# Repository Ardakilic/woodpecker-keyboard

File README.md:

# Woodpecker Keyboard
5 row ortholinear keyboard, based on [Lumberelite](https://github.com/tjeffree/lumberelite) and [Lumberjack](https://github.com/peej/lumberjack-keyboard).

The fork is done in a way that a wireless controller such as [nice!nano](https://nicekeyboards.com/nice-nano/) or [alternatives](https://github.com/joric/nrfmicro/wiki/Alternatives) could be utilized, and OLED module, Pimoroni Trackball or Cirque Trackpad could be applied over to the central area of the keyboard.

All work on the PCB is done by [Özkan Çelik](https://github.com/ozkan), he made this due to my request.

Shields are done by Kazim Kaba and [Ender Piyale](https://github.com/enderpiyale/).

[The plates of Lumberjack Keyboard](https://github.com/peej/lumberjack-keyboard/tree/master/plates) work nicely. I'm currently using the `lumberjack-split` flavour on my board, which you can also find [here](./plates-shields/plates/lumberjack-split.dxf).

Additionally, the board is compatible with 60% cases. My case is a wooden one from a Chinese e-commerce website. I raised the micro controller with sockets to not to drill a hole into my case.

## Firmware

* QMK: Keyboard definition and userspace
    * https://github.com/Ardakilic/qmk_firmware/tree/master/keyboards/woodpecker
    * https://github.com/Ardakilic/qmk_userspace/tree/main/keyboards/woodpecker
* ZMK: https://github.com/ardakilic/zmk-config-woodpecker

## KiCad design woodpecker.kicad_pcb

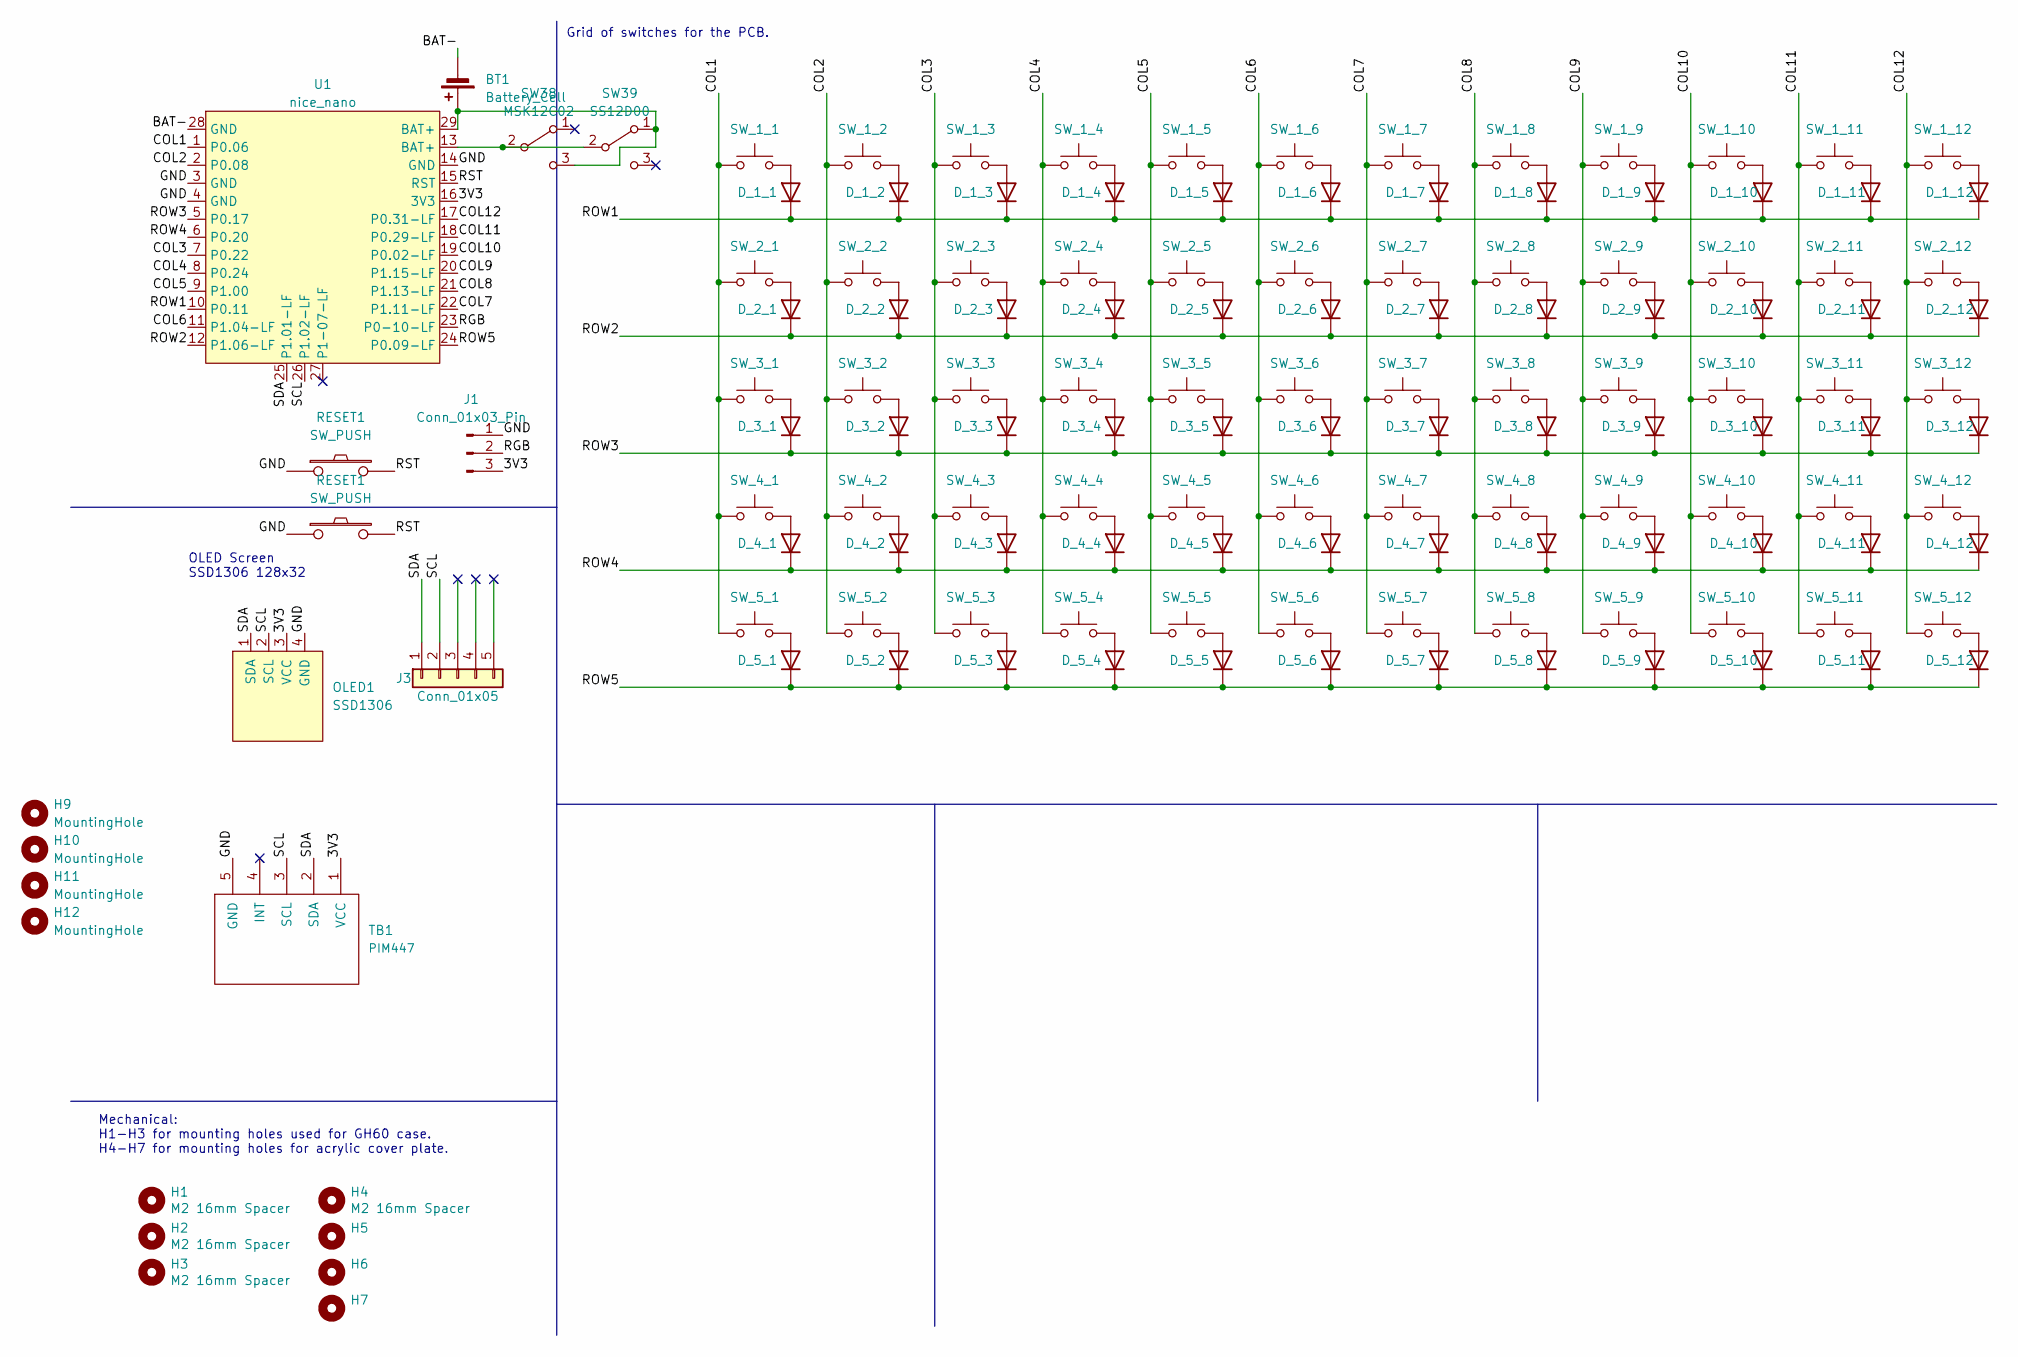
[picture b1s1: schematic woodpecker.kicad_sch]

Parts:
BT1: Battery_Cell; PinHeader_1x02_P2.54mm_Vertical
D_1_1, D_1_2, D_1_3, D_1_4, D_1_5, D_1_6, D_1_7, D_1_8, D_1_9, D_1_10, D_1_11, D_1_12, D_2_1, D_2_2, D_2_3, D_2_4, D_2_5, D_2_6, D_2_7, D_2_8, D_2_9, D_2_10, D_2_11, D_2_12, D_3_1, D_3_2, D_3_3, D_3_4, D_3_5, D_3_6, D_3_7, D_3_8, D_3_9, D_3_10, D_3_11, D_3_12, D_4_1, D_4_2, D_4_3, D_4_4, D_4_5, D_4_6, D_4_7, D_4_8, D_4_9, D_4_10, D_4_11, D_4_12, D_5_1, D_5_2, D_5_3, D_5_4, D_5_5, D_5_6, D_5_7, D_5_8, D_5_9, D_5_10, D_5_11, D_5_12: 1N4148; Diode-dual
H1, H2, H3, H4: M2 16mm Spacer; MountingHole_2.2mm_M2_DIN965_Pad
H5: Bumpon_3M_F0502
H6, H7: MountingHole_2.2mm_M2_elongated
H9, H10, H11, H12: MountingHole; M2_Threads_v2
J1: Conn_01x03_Pin; PinHeader_1x03_P2.54mm_Vertical
J3: Conn_01x05; PinHeader_1x05_P2.54mm_Vertical
OLED1: SSD1306; OLED_v2
RESET1: SW_PUSH; SW_SPST_RS-282G05A3-SM
SW38: MSK12C02
SW39: SS12D00
SW_1_1, SW_1_2, SW_1_3, SW_1_4, SW_1_5, SW_1_6, SW_1_7, SW_1_8, SW_1_9, SW_1_10, SW_1_11, SW_1_12, SW_2_1, SW_2_2, SW_2_3, SW_2_4, SW_2_5, SW_2_6, SW_2_7, SW_2_8, SW_2_9, SW_2_10, SW_2_11, SW_2_12, SW_3_1, SW_3_2, SW_3_3, SW_3_4, SW_3_5, SW_3_6, SW_3_7, SW_3_8, SW_3_9, SW_3_10, SW_3_11, SW_3_12, SW_4_1, SW_4_2, SW_4_3, SW_4_4, SW_4_5, SW_4_6, SW_4_7, SW_4_8, SW_4_9, SW_4_10, SW_4_11, SW_4_12, SW_5_1, SW_5_2, SW_5_3, SW_5_4, SW_5_5, SW_5_6, SW_5_7, SW_5_8, SW_5_9, SW_5_10, SW_5_11, SW_5_12: MX-compatible or Kailh Choc v1; SW_MX_PG1350_NoLed
TB1: PIM447
U1: nice_nano; nice_nano_AH_Reversible

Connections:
/3V3: J1.3, OLED1.3 (VCC), TB1.1 (VCC), U1.16 (3V3)
/BAT-: BT1.2 (-), U1.28 (GND)
/COL1: SW_1_1.1, SW_2_1.1, SW_3_1.1, SW_4_1.1, SW_5_1.1, U1.1 (P0.06)
/COL2: SW_1_2.1, SW_2_2.1, SW_3_2.1, SW_4_2.1, SW_5_2.1, U1.2 (P0.08)
/COL3: SW_1_3.1, SW_2_3.1, SW_3_3.1, SW_4_3.1, SW_5_3.1, U1.7 (P0.22)
/COL4: SW_1_4.1, SW_2_4.1, SW_3_4.1, SW_4_4.1, SW_5_4.1, U1.8 (P0.24)
/COL5: SW_1_5.1, SW_2_5.1, SW_3_5.1, SW_4_5.1, SW_5_5.1, U1.9 (P1.00)
/COL6: SW_1_6.1, SW_2_6.1, SW_3_6.1, SW_4_6.1, SW_5_6.1, U1.11 (P1.04-LF)
/COL7: SW_1_7.1, SW_2_7.1, SW_3_7.1, SW_4_7.1, SW_5_7.1, U1.22 (P1.11-LF)
/COL8: SW_1_8.1, SW_2_8.1, SW_3_8.1, SW_4_8.1, SW_5_8.1, U1.21 (P1.13-LF)
/COL9: SW_1_9.1, SW_2_9.1, SW_3_9.1, SW_4_9.1, SW_5_9.1, U1.20 (P1.15-LF)
/COL10: SW_1_10.1, SW_2_10.1, SW_3_10.1, SW_4_10.1, SW_5_10.1, U1.19 (P0.02-LF)
/COL11: SW_1_11.1, SW_2_11.1, SW_3_11.1, SW_4_11.1, SW_5_11.1, U1.18 (P0.29-LF)
/COL12: SW_1_12.1, SW_2_12.1, SW_3_12.1, SW_4_12.1, SW_5_12.1, U1.17 (P0.31-LF)
/GND: J1.1, OLED1.4 (GND), RESET1.1, TB1.5 (GND), U1.3 (GND), U1.4 (GND), U1.14 (GND); also elsewhere on the board
/RGB: J1.2, U1.23 (P0-10-LF)
/ROW1: D_1_1.1 (K), D_1_2.1 (K), D_1_3.1 (K), D_1_4.1 (K), D_1_5.1 (K), D_1_6.1 (K), D_1_7.1 (K), D_1_8.1 (K), D_1_9.1 (K), D_1_10.1 (K), D_1_11.1 (K), D_1_12.1 (K), U1.10 (P0.11)
/ROW2: D_2_1.1 (K), D_2_2.1 (K), D_2_3.1 (K), D_2_4.1 (K), D_2_5.1 (K), D_2_6.1 (K), D_2_7.1 (K), D_2_8.1 (K), D_2_9.1 (K), D_2_10.1 (K), D_2_11.1 (K), D_2_12.1 (K), U1.12 (P1.06-LF)
/ROW3: D_3_1.1 (K), D_3_2.1 (K), D_3_3.1 (K), D_3_4.1 (K), D_3_5.1 (K), D_3_6.1 (K), D_3_7.1 (K), D_3_8.1 (K), D_3_9.1 (K), D_3_10.1 (K), D_3_11.1 (K), D_3_12.1 (K), U1.5 (P0.17)
/ROW4: D_4_1.1 (K), D_4_2.1 (K), D_4_3.1 (K), D_4_4.1 (K), D_4_5.1 (K), D_4_6.1 (K), D_4_7.1 (K), D_4_8.1 (K), D_4_9.1 (K), D_4_10.1 (K), D_4_11.1 (K), D_4_12.1 (K), U1.6 (P0.20)
/ROW5: D_5_1.1 (K), D_5_2.1 (K), D_5_3.1 (K), D_5_4.1 (K), D_5_5.1 (K), D_5_6.1 (K), D_5_7.1 (K), D_5_8.1 (K), D_5_9.1 (K), D_5_10.1 (K), D_5_11.1 (K), D_5_12.1 (K), U1.24 (P0.09-LF)
/RST: RESET1.2, U1.15 (RST); also elsewhere on the board
/SCL: OLED1.2 (SCL), TB1.3 (SCL), U1.26 (P1.02-LF); also elsewhere on the board
/SDA: OLED1.1 (SDA), TB1.2 (SDA), U1.25 (P1.01-LF); also elsewhere on the board
unnamed 24: BT1.1 (+), U1.29 (BAT+); also elsewhere on the board
unnamed: D_1_1.2 (A), SW_1_1.2
unnamed: D_1_2.2 (A), SW_1_2.2
unnamed: D_1_3.2 (A), SW_1_3.2
unnamed: D_1_4.2 (A), SW_1_4.2
unnamed: D_1_5.2 (A), SW_1_5.2
unnamed: D_1_6.2 (A), SW_1_6.2
unnamed: D_1_7.2 (A), SW_1_7.2
unnamed: D_1_8.2 (A), SW_1_8.2
unnamed: D_1_9.2 (A), SW_1_9.2
unnamed: D_1_10.2 (A), SW_1_10.2
unnamed: D_1_11.2 (A), SW_1_11.2
unnamed: D_1_12.2 (A), SW_1_12.2
unnamed: D_2_1.2 (A), SW_2_1.2
unnamed: D_2_2.2 (A), SW_2_2.2
unnamed: D_2_3.2 (A), SW_2_3.2
unnamed: D_2_4.2 (A), SW_2_4.2
unnamed: D_2_5.2 (A), SW_2_5.2
unnamed: D_2_6.2 (A), SW_2_6.2
unnamed: D_2_7.2 (A), SW_2_7.2
unnamed: D_2_8.2 (A), SW_2_8.2
unnamed: D_2_9.2 (A), SW_2_9.2
unnamed: D_2_10.2 (A), SW_2_10.2
unnamed: D_2_11.2 (A), SW_2_11.2
unnamed: D_2_12.2 (A), SW_2_12.2
unnamed: D_3_1.2 (A), SW_3_1.2
unnamed: D_3_2.2 (A), SW_3_2.2
unnamed: D_3_3.2 (A), SW_3_3.2
unnamed: D_3_4.2 (A), SW_3_4.2
unnamed: D_3_5.2 (A), SW_3_5.2
unnamed: D_3_6.2 (A), SW_3_6.2
unnamed: D_3_7.2 (A), SW_3_7.2
unnamed: D_3_8.2 (A), SW_3_8.2
unnamed: D_3_9.2 (A), SW_3_9.2
unnamed: D_3_10.2 (A), SW_3_10.2
unnamed: D_3_11.2 (A), SW_3_11.2
unnamed: D_3_12.2 (A), SW_3_12.2
unnamed: D_4_1.2 (A), SW_4_1.2
unnamed: D_4_2.2 (A), SW_4_2.2
unnamed: D_4_3.2 (A), SW_4_3.2
unnamed: D_4_4.2 (A), SW_4_4.2
unnamed: D_4_5.2 (A), SW_4_5.2
unnamed: D_4_6.2 (A), SW_4_6.2
unnamed: D_4_7.2 (A), SW_4_7.2
unnamed: D_4_8.2 (A), SW_4_8.2
unnamed: D_4_9.2 (A), SW_4_9.2
unnamed: D_4_10.2 (A), SW_4_10.2
unnamed: D_4_11.2 (A), SW_4_11.2
unnamed: D_4_12.2 (A), SW_4_12.2
unnamed: D_5_1.2 (A), SW_5_1.2
unnamed: D_5_2.2 (A), SW_5_2.2
unnamed: D_5_3.2 (A), SW_5_3.2
unnamed: D_5_4.2 (A), SW_5_4.2
unnamed: D_5_5.2 (A), SW_5_5.2
unnamed: D_5_6.2 (A), SW_5_6.2
unnamed: D_5_7.2 (A), SW_5_7.2
unnamed: D_5_8.2 (A), SW_5_8.2
unnamed: D_5_9.2 (A), SW_5_9.2
unnamed: D_5_10.2 (A), SW_5_10.2
unnamed: D_5_11.2 (A), SW_5_11.2
unnamed: D_5_12.2 (A), SW_5_12.2
unnamed 85: U1.13 (BAT+); also elsewhere on the board

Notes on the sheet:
Grid of switches for the PCB.
OLED Screen SSD1306 128x32
Mechanical: H1-H3 for mounting holes used for GH60 case. H4-H7 for mounting holes for acrylic cover plate.

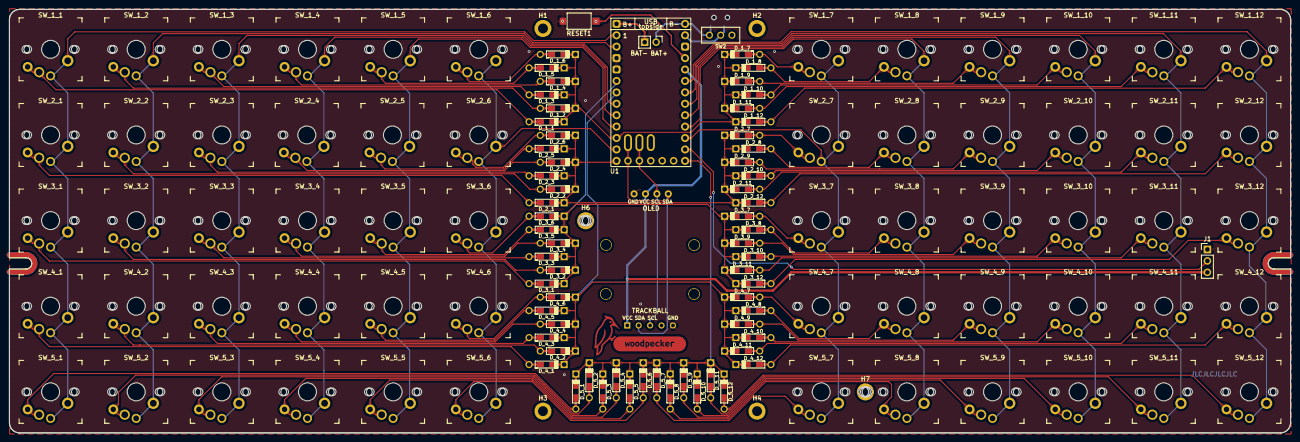
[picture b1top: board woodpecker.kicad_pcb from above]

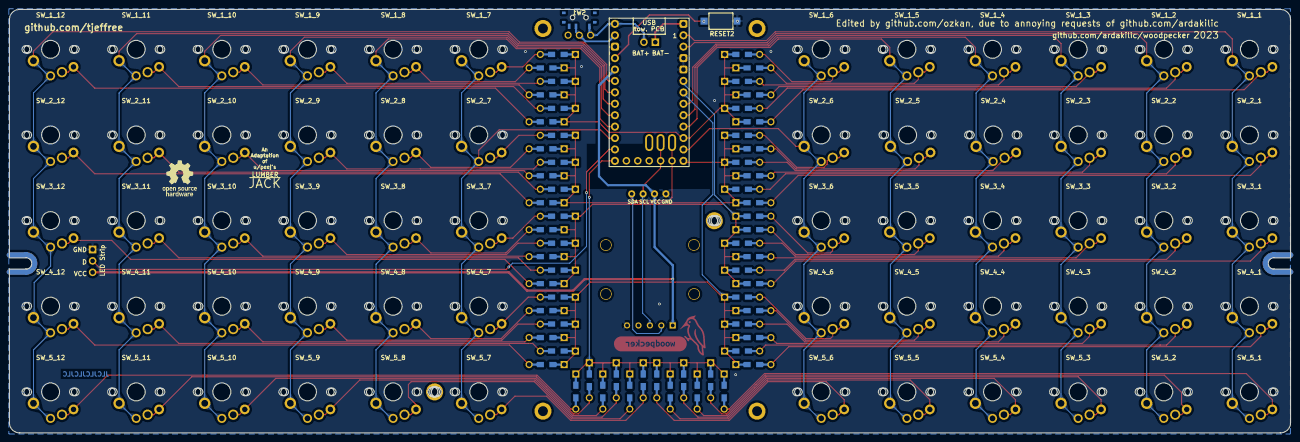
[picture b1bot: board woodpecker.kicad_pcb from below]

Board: 2 copper layers, 285.0 x 94.2 mm, 144 parts (2 on the bottom side), 86 nets.

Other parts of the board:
H8: MountingHole; M2_Threads_v2
HOLE: Graphic_Mask_HalfHole
HOLE#2: Graphic_Mask_HalfHole
J2: Conn_01x05; PinHeader_1x05_P2.54mm_Vertical
RESET2: SW_PUSH; SW_SPST_RS-282G05A3-SM
SW1: MSK12C02
SW2: SS12D00
kibuzzard-656122B9: G***; kibuzzard-656122B9

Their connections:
/GND: RESET2.1; also elsewhere on the board
/RST: RESET2.2; also elsewhere on the board
/SCL: J2.2; also elsewhere on the board
/SDA: J2.1; also elsewhere on the board
unnamed 24: SW1.3 (C), SW2.1 (A); also elsewhere on the board
unnamed 85: SW1.2 (B), SW2.2 (B); also elsewhere on the board

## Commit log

2024-03-25 Upload the board to GitHub
2024-03-25 include bom and pos files, modify gitignore
2024-04-11 Shields added, thanks to @enderpiyale
2024-07-21 chore: copy add lumberjack split plate into the repository, clean up README
2024-10-27 feature: shield f3d project added
